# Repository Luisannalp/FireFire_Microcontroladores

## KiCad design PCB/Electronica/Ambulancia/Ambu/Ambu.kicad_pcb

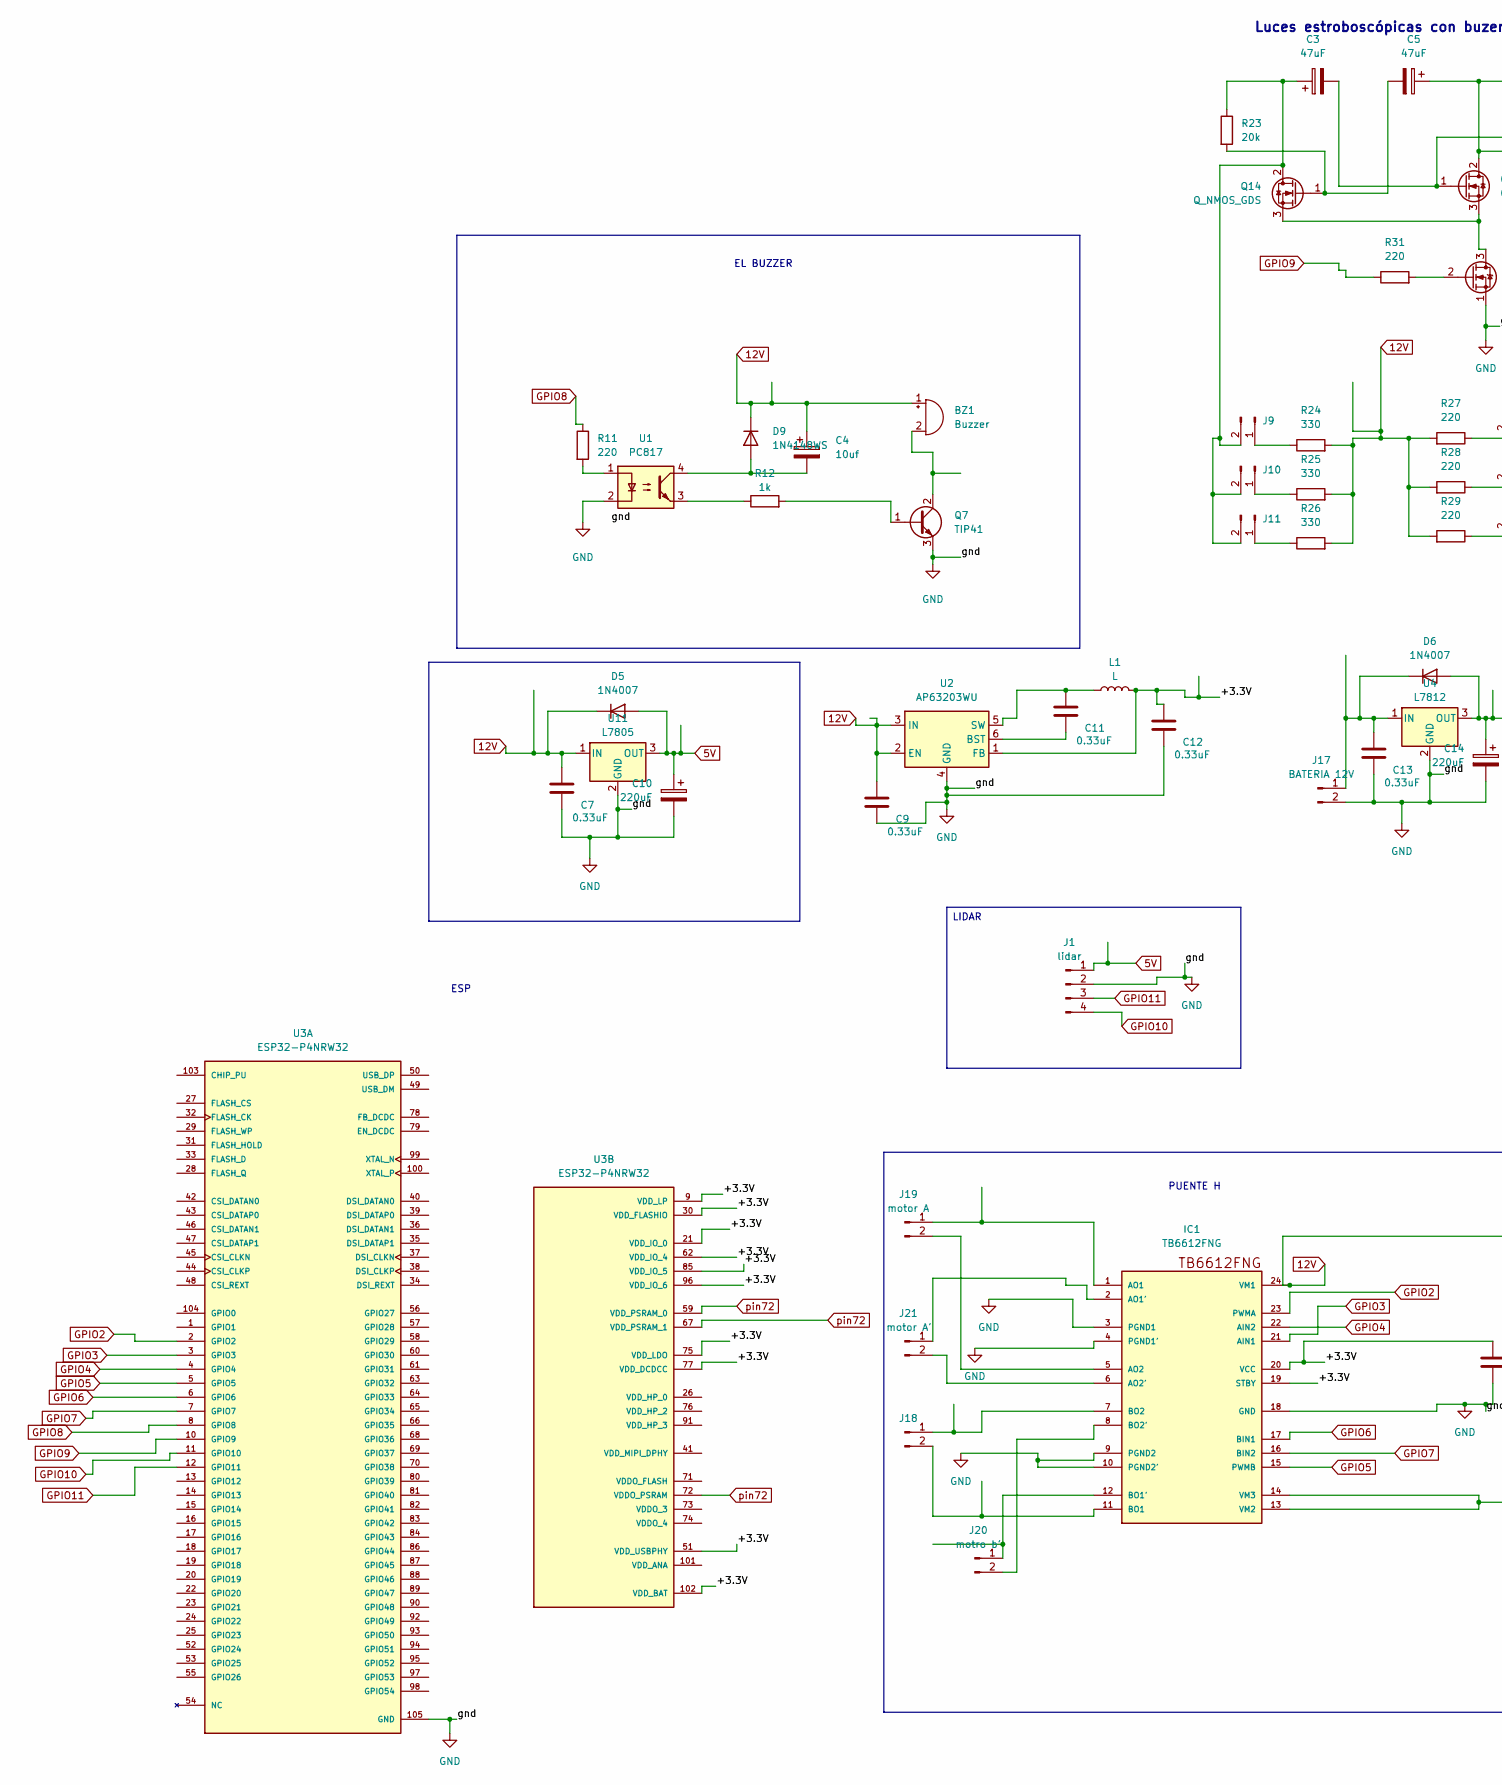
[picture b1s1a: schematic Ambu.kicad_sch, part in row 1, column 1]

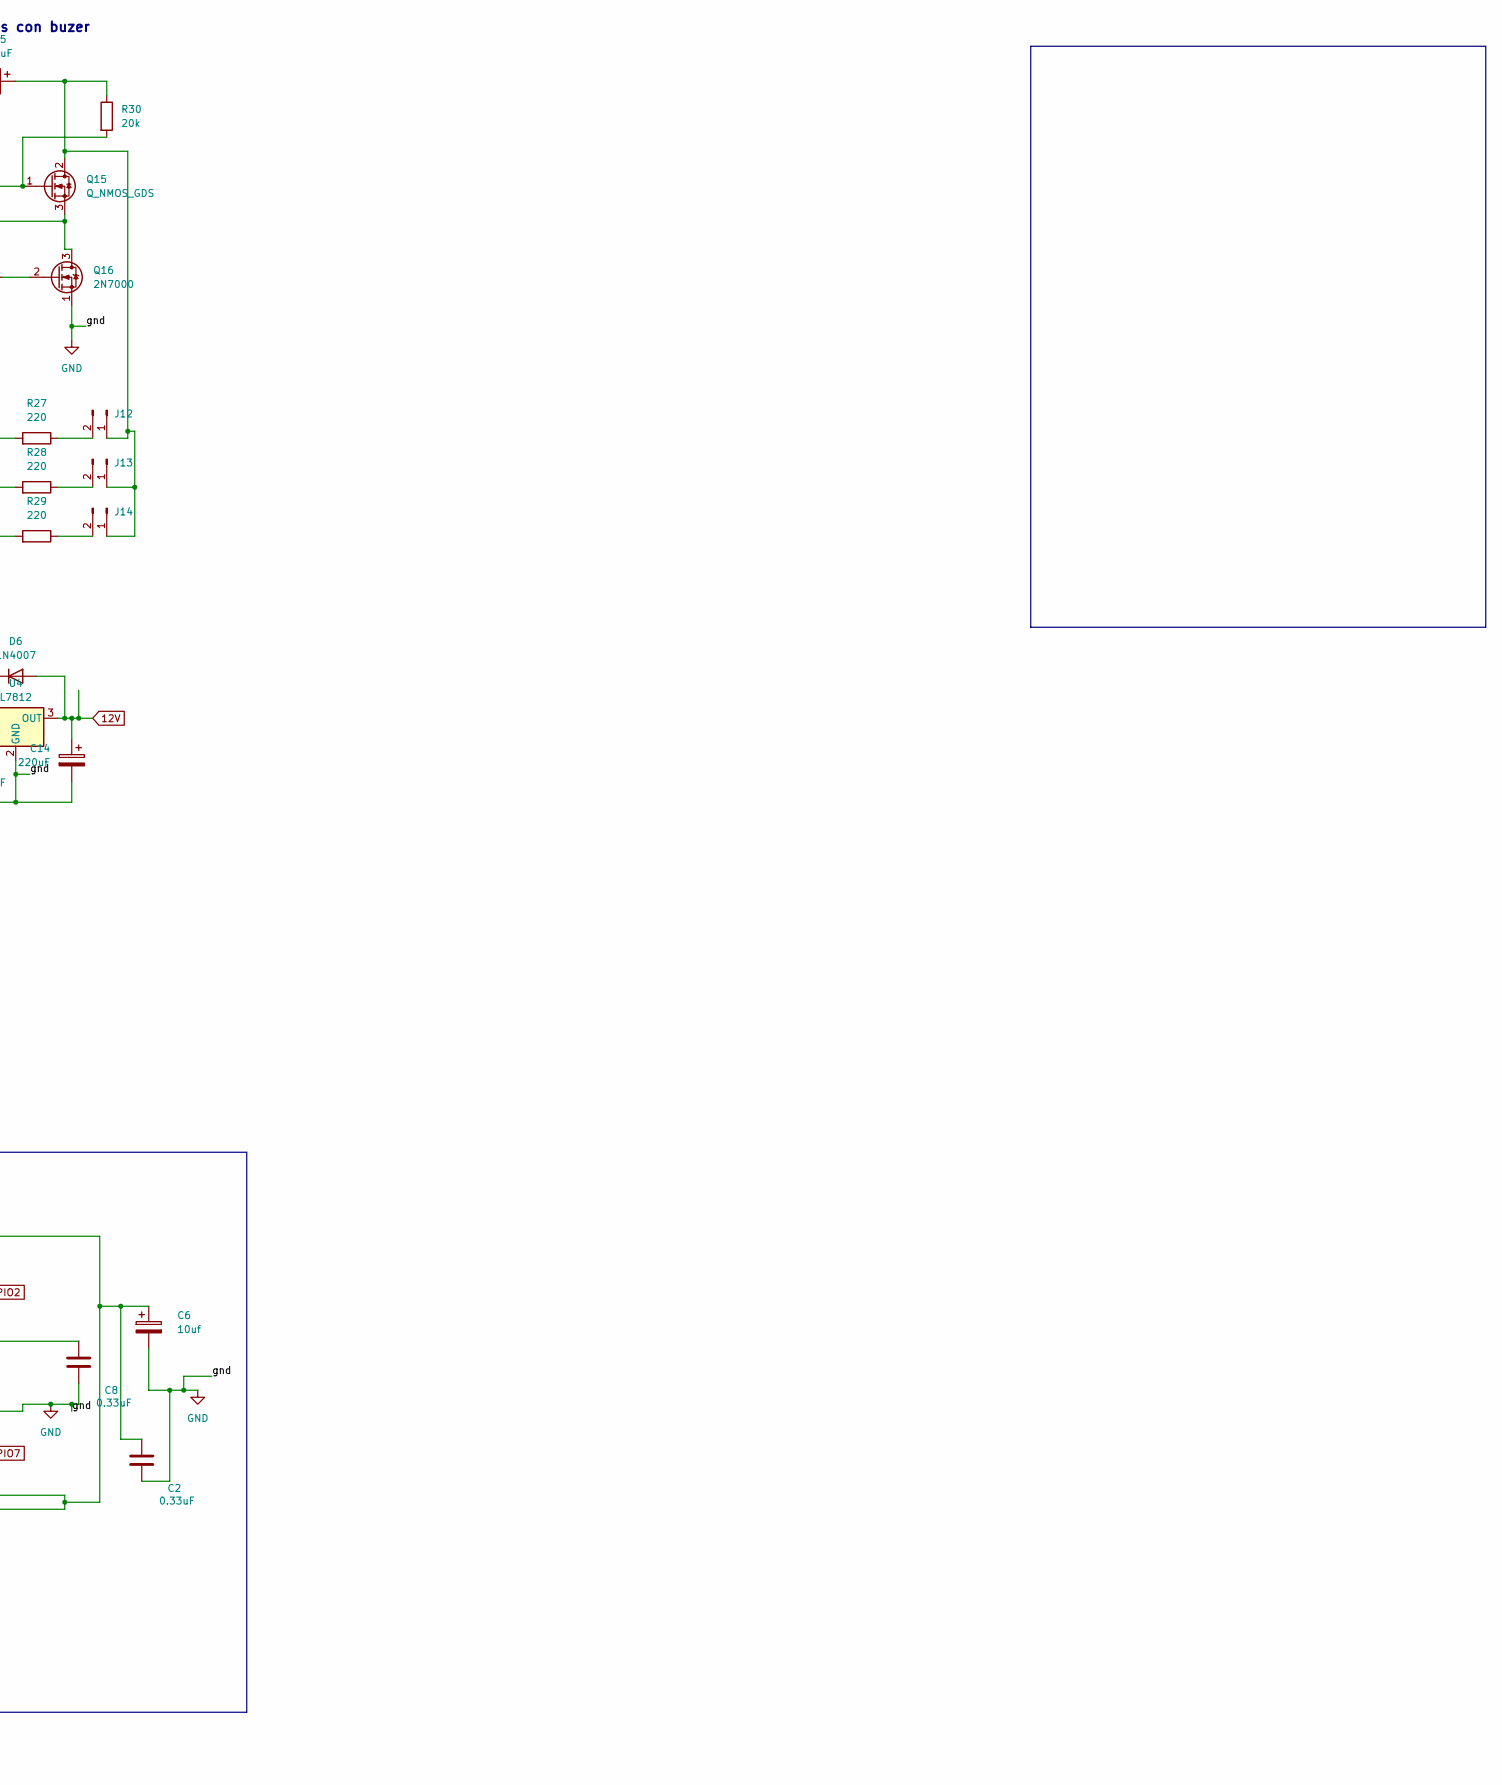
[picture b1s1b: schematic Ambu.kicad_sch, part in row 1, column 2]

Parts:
BZ1: Buzzer; Buzzer_12x9.5RM7.6
C2, C7, C8, C9, C11, C12, C13: 0.33uF; C_Disc_D3.0mm_W2.0mm_P2.50mm
C3, C5: 47uF; CP_Radial_D8.0mm_P3.50mm
C4, C6: 10uf; CP_Radial_D6.3mm_P2.50mm
C10, C14: 220uF; CP_Radial_D6.3mm_P2.50mm
D5, D6: 1N4007; D_DO-41_SOD81_P10.16mm_Horizontal
D9: 1N4148WS; D_SOD-323
IC1: TB6612FNG; SSOP24; MPN TB6612FNG
J1: lidar; Molex_KK-254_AE-6410-04A_1x04_P2.54mm_Vertical
J9, J10, J11, J12, J13, J14: Molex_KK-254_AE-6410-02A_1x02_P2.54mm_Vertical
J17: BATERIA 12V; Molex_KK-254_AE-6410-02A_1x02_P2.54mm_Vertical
J18: MOTOR B; Molex_KK-254_AE-6410-02A_1x02_P2.54mm_Vertical
J19: motor A; Molex_KK-254_AE-6410-02A_1x02_P2.54mm_Vertical
J20: motro b'; Molex_KK-254_AE-6410-02A_1x02_P2.54mm_Vertical
J21: motor A'; Molex_KK-254_AE-6410-02A_1x02_P2.54mm_Vertical
L1: L
Q7: TIP41; TO-220-3_Vertical
Q14, Q15: Q_NMOS_GDS; TO-220-3_Vertical
Q16: 2N7000; TO-92_Inline
R11: 220; R_2010_5025Metric
R12: 1k; R_2010_5025Metric
R23, R30: 20k; R_1206_3216Metric_Pad1.30x1.75mm_HandSolder
R24, R25, R26: 330; R_1206_3216Metric_Pad1.30x1.75mm_HandSolder
R27, R28, R29, R31: 220; R_1206_3216Metric_Pad1.30x1.75mm_HandSolder
U1: PC817; DIP-4_W7.62mm
U2: AP63203WU; TSOT-23-6
U3: ESP32-P4NRW32; IC_ESP32-P4NRW32; MPN ESP32-P4NRW32
U4: L7812; TO-220-3_Vertical
U11: L7805; TO-220-3_Vertical

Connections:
5V: C10.1, D5.2 (A), J1.1, U11.3 (OUT)
12V: BZ1.1 (+), C2.1, C4.1, C6.1, C7.1, C9.1, C14.1, D5.1 (K), D6.2 (A), D9.1 (K), IC1.13 (VM2), IC1.14 (VM3), IC1.24 (VM1), R24.2, R25.2, R26.2, R27.2, R28.2, R29.2, U2.2 (EN), U2.3 (IN), U4.3 (OUT), U11.1 (IN)
/+3.3V: C8.1, C12.1, IC1.19 (STBY), IC1.20 (VCC), L1.2, U2.1 (FB), U3.9 (VDD_LP), U3.21 (VDD_IO_0), U3.30 (VDD_FLASHIO), U3.51 (VDD_USBPHY), U3.62 (VDD_IO_4), U3.75 (VDD_LDO), U3.77 (VDD_DCDCC), U3.85 (VDD_IO_5), U3.96 (VDD_IO_6), U3.102 (VDD_BAT)
GND: C2.2, C6.2, C7.2, C8.2, C9.2, C10.2, C12.2, C13.2, C14.2, IC1.3 (PGND1), IC1.4 (PGND1'), IC1.9 (PGND2), IC1.10 (PGND2'), IC1.18 (GND), J1.2, J17.2, Q7.3 (E), Q16.1 (S), U1.2, U2.4 (GND), U3.105 (GND), U4.2 (GND), U11.2 (GND)
GPIO2: IC1.23 (PWMA), U3.2 (GPIO2)
GPIO3: IC1.21 (AIN1), U3.3 (GPIO3)
GPIO4: IC1.22 (AIN2), U3.4 (GPIO4)
GPIO5: IC1.15 (PWMB), U3.5 (GPIO5)
GPIO6: IC1.17 (BIN1), U3.6 (GPIO6)
GPIO7: IC1.16 (BIN2), U3.7 (GPIO7)
GPIO8: R11.1, U3.8 (GPIO8)
GPIO9: R31.1, U3.10 (GPIO9)
GPIO10: J1.4, U3.11 (GPIO10)
GPIO11: J1.3, U3.12 (GPIO11)
unnamed: BZ1.2 (-), Q7.2 (C)
unnamed: C13.1, D6.1 (K), J17.1, U4.1 (IN)
unnamed: C4.2, D9.2 (A), U1.4
unnamed: IC1.2 (AO1'), J21.1
unnamed: IC1.1 (AO1), J19.1
unnamed: IC1.6 (AO2'), J21.2
unnamed: IC1.5 (AO2), J19.2
unnamed: IC1.12 (BO1'), J20.1
unnamed: IC1.11 (BO1), J18.2
unnamed: IC1.8 (BO2'), J20.2
unnamed: IC1.7 (BO2), J18.1
unnamed: J9.1, R24.1
unnamed: J10.1, R25.1
unnamed: C3.1, J9.2, J10.2, J11.2, Q14.2 (D), R23.1
unnamed: J11.1, R26.1
unnamed: C5.1, J12.1, J13.1, J14.1, Q15.2 (D), R30.1
unnamed: J12.2, R27.1
unnamed: J13.2, R28.1
unnamed: J14.2, R29.1
unnamed: Q7.1 (B), R12.2
unnamed: C5.2, Q14.1 (G), R23.2
unnamed: Q14.3 (S), Q15.3 (S), Q16.3 (D)
unnamed: C3.2, Q15.1 (G), R30.2
unnamed: Q16.2 (G), R31.2
unnamed: R11.2, U1.1
unnamed: R12.1, U1.3
unnamed: C11.2, U2.6 (BST)
unnamed: C11.1, L1.1, U2.5 (SW)
pin72: U3.59 (VDD_PSRAM_0), U3.67 (VDD_PSRAM_1), U3.72 (VDDO_PSRAM)

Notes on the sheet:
EL BUZZER
ESP
Luces estroboscópicas con buzer
PUENTE H
LIDAR

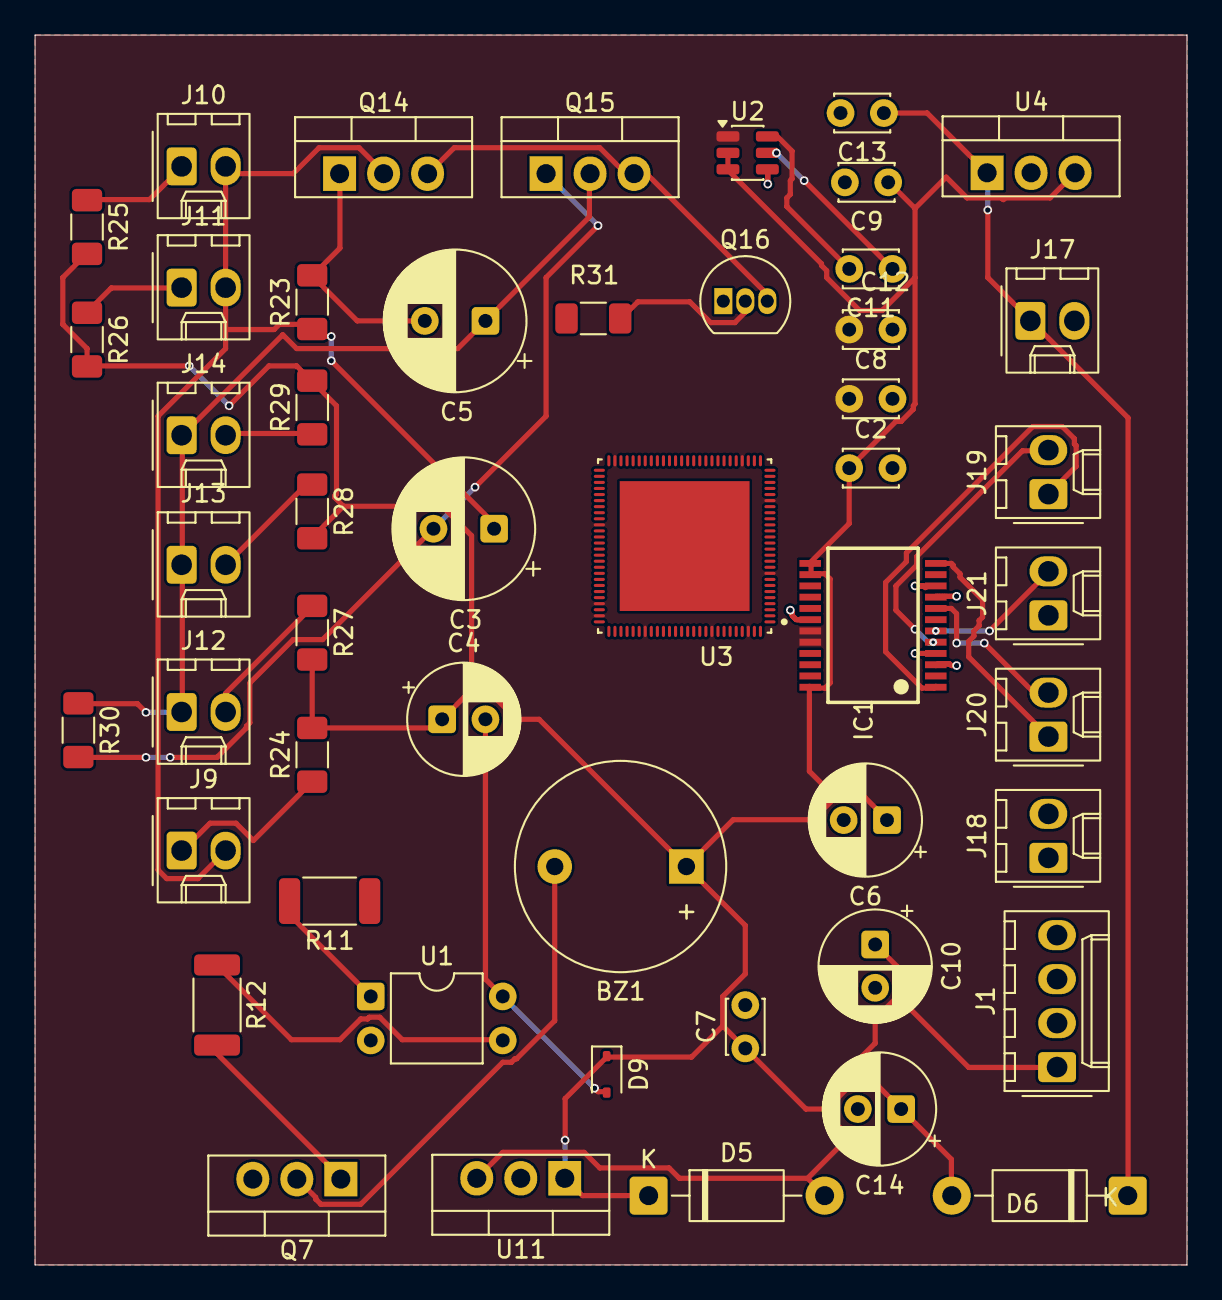
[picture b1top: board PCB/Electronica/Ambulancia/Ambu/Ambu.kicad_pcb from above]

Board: 2 copper layers, 66.5 x 71.0 mm, 50 parts (0 on the bottom side), 43 nets.

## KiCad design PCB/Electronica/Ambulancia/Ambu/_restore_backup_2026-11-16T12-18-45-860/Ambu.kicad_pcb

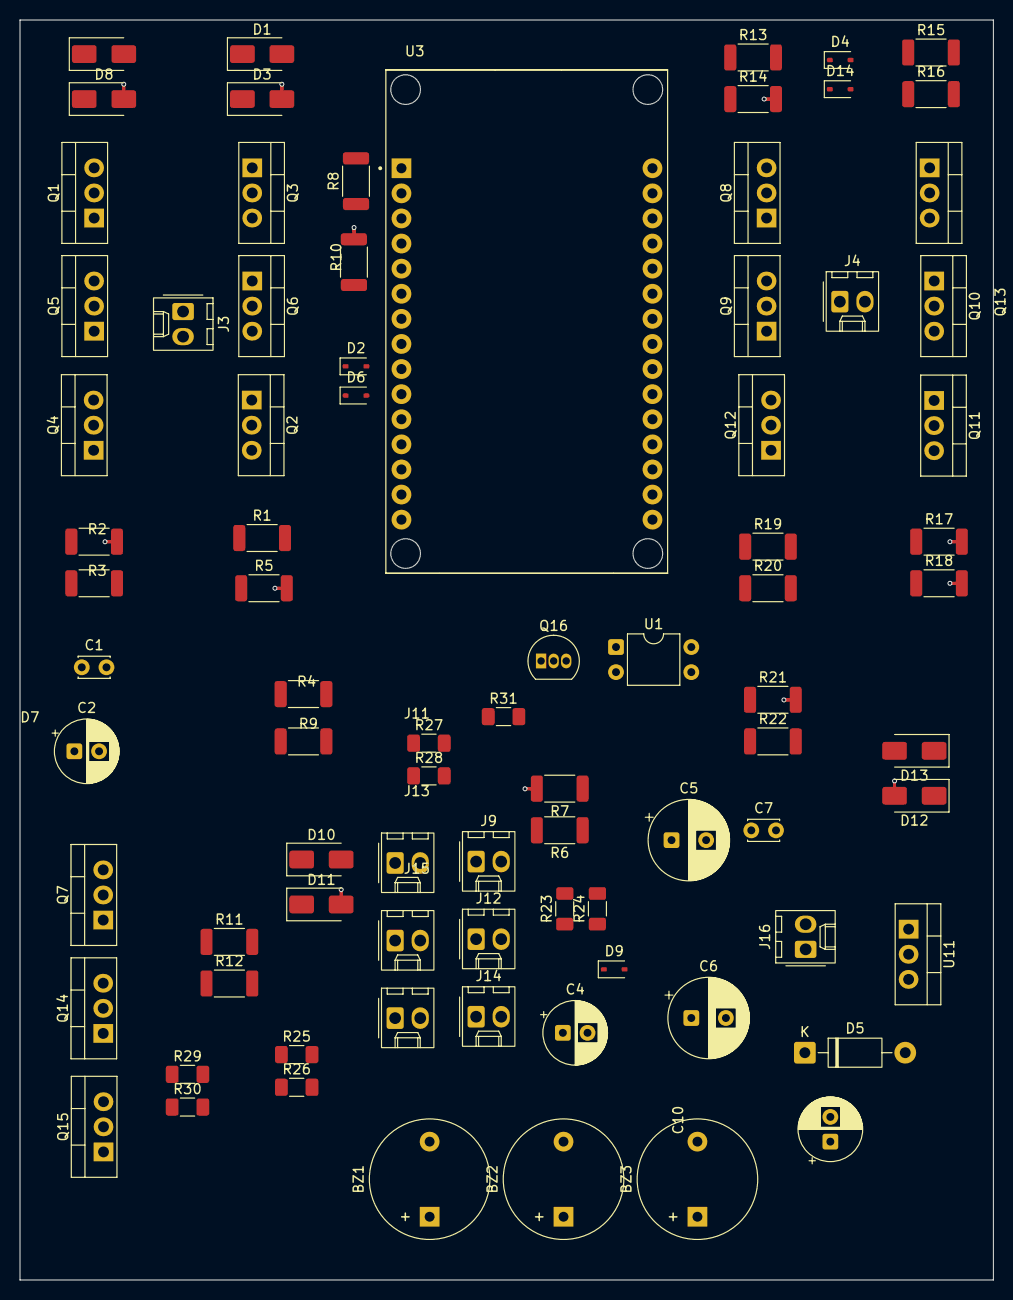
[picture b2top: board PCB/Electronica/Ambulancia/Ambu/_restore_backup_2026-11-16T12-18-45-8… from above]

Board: 2 copper layers, 98.5 x 127.5 mm, 83 parts (0 on the bottom side), 43 nets.

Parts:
BZ1, BZ2, BZ3: Buzzer; Buzzer_12x9.5RM7.6
C1: 100nf; C_Disc_D3.0mm_W2.0mm_P2.50mm
C2: 1000uf; CP_Radial_D6.3mm_P2.50mm
C4: 10uf; CP_Radial_D6.3mm_P2.50mm
C5, C6: 47uF; CP_Radial_D8.0mm_P3.50mm
C7: 0.33uF; C_Disc_D3.0mm_W2.0mm_P2.50mm
C10: 220uF; CP_Radial_D6.3mm_P2.50mm
D1, D3, D7, D8, D10, D11, D12, D13: SS34; D_SMA
D2, D4, D6, D9, D14: 1N4148WS; D_SOD-323
D5: 1N4007; D_DO-41_SOD81_P10.16mm_Horizontal
J3, J4: MOTOR IZ2; Molex_KK-254_AE-6410-02A_1x02_P2.54mm_Vertical
J9, J11, J12, J13, J14, J15: Molex_KK-254_AE-6410-02A_1x02_P2.54mm_Vertical
J16: BATERIA 12V; Molex_KK-254_AE-6410-02A_1x02_P2.54mm_Vertical
Q1, Q3, Q5, Q6, Q9, Q10, Q11, Q12: Q_PMOS_GDS; TO-220-3_Vertical
Q2, Q4, Q8, Q13: AO3400A; TO-220-3_Vertical
Q7: TIP41; TO-220-3_Vertical
Q14, Q15: Q_NMOS_GDS; TO-220-3_Vertical
Q16: 2N7000; TO-92_Inline
R1, R6, R13, R22: 45; R_2010_5025Metric
R2, R3, R7, R9, R10, R14, R16, R18, R19, R21: 10k; R_2010_5025Metric
R4, R8, R15, R20: 47; R_2010_5025Metric
R5, R17: 10; R_2010_5025Metric
R11: 220; R_2010_5025Metric
R12: 1k; R_2010_5025Metric
R23, R30: 20k; R_1206_3216Metric_Pad1.30x1.75mm_HandSolder
R24, R25, R26: 330; R_1206_3216Metric_Pad1.30x1.75mm_HandSolder
R27, R28, R29, R31: 220; R_1206_3216Metric_Pad1.30x1.75mm_HandSolder
U1: PC817; DIP-4_W7.62mm
U3: ESP32-DEVKIT-V1; MODULE_ESP32_DEVKIT_V1
U11: L7805; TO-220-3_Vertical

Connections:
5V: BZ2.1 (+), BZ3.1 (+), C10.1, D5.2 (A), R24.2, R25.2, R26.2, R27.2, R28.2, R29.2, U3.30 (VIN), U11.3 (OUT)
12V: BZ1.1 (+), C1.1, C2.1, C4.1, C7.1, D1.1 (K), D5.1 (K), D7.1 (K), D9.1 (K), D10.1 (K), D13.1 (K), J16.1, Q1.3 (S), Q5.3 (S), Q9.3 (S), Q12.3 (S), R3.2, R9.2, R16.2, R19.2, U11.1 (IN)
GND: C1.2, C2.2, C7.2, C10.2, D3.2 (A), D8.2 (A), D11.2 (A), D12.2 (A), J16.2, Q2.2 (S), Q3.3 (S), Q4.2 (S), Q6.3 (S), Q7.3 (E), Q8.2 (S), Q10.3 (S), Q11.3 (S), Q13.2 (S), Q16.1 (S), R2.2, R5.2, R7.2, R10.2, R14.2, R17.2, R18.2, R21.2, U1.2, U3.2 (GND), U3.29 (GND), U11.2 (GND)
GPIO25: R11.1, U3.23 (D25)
GPIO26: R1.1, R13.1, U3.26 (D14)
GPIO27: R6.1, R22.1, U3.27 (D12)
unnamed: BZ1.2 (-), Q7.2 (C)
unnamed: BZ2.2 (-), C6.1, J13.1, J14.1, J15.1, Q15.2 (D), R30.1
unnamed: BZ3.2 (-), C5.1, J9.2, J11.2, J12.2, Q14.2 (D), R23.1
unnamed: D1.2 (A), D3.1 (K), J3.2, Q1.2 (D), Q3.2 (D)
unnamed: D2.2 (A), Q3.1 (G), R4.2, R5.1
unnamed: D2.1 (K), R4.1
unnamed: D4.2 (A), Q10.1 (G), R15.2, R17.1
unnamed: D4.1 (K), R15.1
unnamed: D6.2 (A), Q6.1 (G), R8.2, R10.1
unnamed: D6.1 (K), R8.1
unnamed: D7.2 (A), D8.1 (K), J3.1, Q5.2 (D), Q6.2 (D)
unnamed: C4.2, D9.2 (A), U1.4
unnamed: D10.2 (A), D11.1 (K), J4.2, Q9.2 (D), Q10.2 (D)
unnamed: D12.1 (K), D13.2 (A), J4.1, Q11.2 (D), Q12.2 (D)
unnamed: D14.2 (A), Q11.1 (G), R18.1, R20.2
unnamed: D14.1 (K), R20.1
unnamed: J9.1, R24.1
unnamed: J11.1, R25.1
unnamed: J12.1, R26.1
unnamed: J13.2, R27.1
unnamed: J14.2, R28.1
unnamed: J15.2, R29.1
unnamed: Q1.1 (G), Q2.3 (D), R3.1
unnamed: Q2.1 (G), R1.2, R2.1
unnamed: Q4.3 (D), Q5.1 (G), R9.1
unnamed: Q4.1 (G), R6.2, R7.1
unnamed: Q7.1 (B), R12.2
unnamed: Q8.3 (D), Q9.1 (G), R16.1
unnamed: Q8.1 (G), R13.2, R14.1
unnamed: Q12.1 (G), Q13.3 (D), R19.1
unnamed: Q13.1 (G), R21.1, R22.2
unnamed: C6.2, Q14.1 (G), R23.2
unnamed: Q14.3 (S), Q15.3 (S), Q16.3 (D)
unnamed: C5.2, Q15.1 (G), R30.2
unnamed: Q16.2 (G), R31.2
unnamed: R11.2, U1.1
unnamed: R12.1, U1.3
